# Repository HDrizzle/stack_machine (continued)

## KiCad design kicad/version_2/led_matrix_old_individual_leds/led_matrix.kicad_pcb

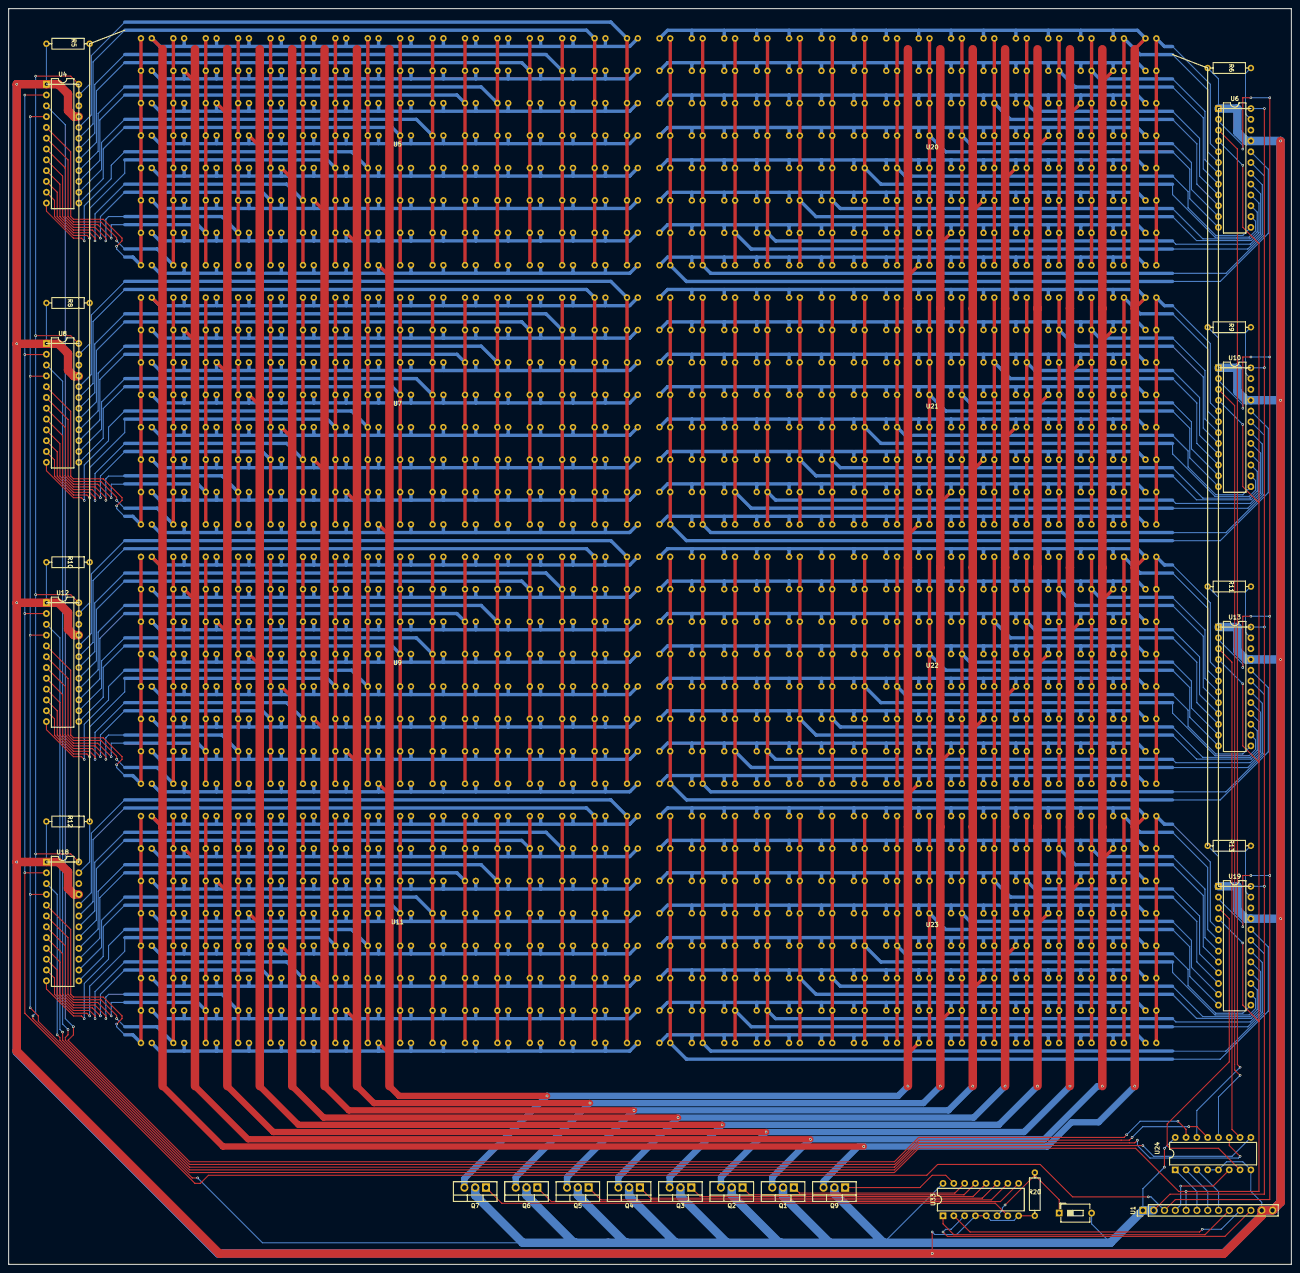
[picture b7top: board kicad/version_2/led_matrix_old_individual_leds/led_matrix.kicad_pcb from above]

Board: 2 copper layers, 301.6 x 295.3 mm, 37 parts (0 on the bottom side), 172 nets.

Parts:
Q1, Q2, Q3, Q4, Q5, Q6, Q7, Q9: IRF540N; TO-220-3_Vertical
R5, R6, R8, R9, R10, R11, R12, R13, R20: R; 0.4_pitch_resistor
SW1: SW_DIP_x01; SW_DIP_SPSTx01_Slide_6.7x4.1mm_W7.62mm_P2.54mm_LowProfile
U1: PinHeader_1x13_P2.54mm_Vertical
U4, U6, U8, U10, U12, U13, U18, U19: DIP-24_W7.62mm
U5, U7, U9, U11: led_block_16_x_8_left
U20, U21, U22, U23: led_block_16_x_8_right
U24, U33: DIP-16_W7.62mm

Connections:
unnamed: Q1.2 (D), Q2.2 (D), Q3.2 (D), Q4.2 (D), Q5.2 (D), Q6.2 (D), Q7.2 (D), Q9.2 (D), SW1.2, U1.1 (V+), U1.2 (V+), U4.24 (V+), U6.24 (V+), U8.24 (V+), U10.24 (V+), U12.24 (V+), U13.24 (V+), U18.24 (V+), U19.24 (V+), U24.16 (V+), U33.16 (V+)
unnamed: Q1.1 (G), U33.14 (Y1)
unnamed: Q1.3 (S), U5.18 (R1), U7.18 (R1), U9.18 (R1), U11.18 (R1), U20.18 (R1), U21.18 (R1), U22.18 (R1), U23.18 (R1)
unnamed: Q2.1 (G), U33.13 (Y2)
unnamed: Q2.3 (S), U5.19 (R2), U7.19 (R2), U9.19 (R2), U11.19 (R2), U20.19 (R2), U21.19 (R2), U22.19 (R2), U23.19 (R2)
unnamed: Q3.1 (G), U33.12 (Y3)
unnamed: Q3.3 (S), U5.20 (R3), U7.20 (R3), U9.20 (R3), U11.20 (R3), U20.20 (R3), U21.20 (R3), U22.20 (R3), U23.20 (R3)
unnamed: Q4.1 (G), U33.11 (Y4)
unnamed: Q4.3 (S), U5.21 (R4), U7.21 (R4), U9.21 (R4), U11.21 (R4), U20.21 (R4), U21.21 (R4), U22.21 (R4), U23.21 (R4)
unnamed: Q5.1 (G), U33.10 (Y5)
unnamed: Q5.3 (S), U5.22 (R5), U7.22 (R5), U9.22 (R5), U11.22 (R5), U20.22 (R5), U21.22 (R5), U22.22 (R5), U23.22 (R5)
unnamed: Q6.1 (G), U33.9 (Y6)
unnamed: Q6.3 (S), U5.23 (R6), U7.23 (R6), U9.23 (R6), U11.23 (R6), U20.23 (R6), U21.23 (R6), U22.23 (R6), U23.23 (R6)
unnamed: Q7.1 (G), U33.7 (Y7)
unnamed: Q7.3 (S), U5.24 (R7), U7.24 (R7), U9.24 (R7), U11.24 (R7), U20.24 (R7), U21.24 (R7), U22.24 (R7), U23.24 (R7)
unnamed: Q9.1 (G), U33.15 (Y0)
unnamed: Q9.3 (S), U5.17 (R0), U7.17 (R0), U9.17 (R0), U11.17 (R0), U20.17 (R0), U21.17 (R0), U22.17 (R0), U23.17 (R0)
unnamed: U1.4 (CLK), U24.6 (E1)
unnamed: U1.3 (Data), U4.2 (D_in), U6.2 (D_in), U8.2 (D_in), U10.2 (D_in), U12.2 (D_in), U13.2 (D_in), U18.2 (D_in), U19.2 (D_in)
unnamed: U1.6 (Driver_A0), U24.1 (A0)
unnamed: U1.7 (Driver_A1), U24.2 (A1)
unnamed: U1.8 (Driver_A2), U24.3 (A2)
unnamed: U1.5 (Driver_LE), U4.4 (LE), U6.4 (LE), U8.4 (LE), U10.4 (LE), U12.4 (LE), U13.4 (LE), U18.4 (LE), U19.4 (LE)
unnamed: U1.9 (Row_A0), U33.1 (A0)
unnamed: U1.10 (Row_A1), U33.2 (A1)
unnamed: U1.11 (Row_A2), U33.3 (A2)
unnamed: U4.5 (O0), U5.1 (C0)
unnamed: U4.6 (O1), U5.2 (C1)
unnamed: U4.7 (O2), U5.3 (C2)
unnamed: U4.8 (O3), U5.4 (C3)
unnamed: U4.9 (O4), U5.5 (C4)
unnamed: U4.10 (O5), U5.6 (C5)
unnamed: U4.11 (O6), U5.7 (C6)
unnamed: U4.12 (O7), U5.8 (C7)
unnamed: U4.13 (O8), U5.9 (C8)
unnamed: U4.14 (O9), U5.10 (C9)
unnamed: U4.15 (O10), U5.11 (C10)
unnamed: U4.16 (O11), U5.12 (C11)
unnamed: U4.17 (O12), U5.13 (C12)
unnamed: U4.18 (O13), U5.14 (C13)
unnamed: U4.19 (O14), U5.15 (C14)
unnamed: U4.20 (O15), U5.16 (C15)
unnamed: R5.1, U4.23 (SET)
unnamed: R6.1, U6.23 (SET)
unnamed: U7.1 (C0), U8.5 (O0)
unnamed: U7.2 (C1), U8.6 (O1)
unnamed: U7.3 (C2), U8.7 (O2)
unnamed: U7.4 (C3), U8.8 (O3)
unnamed: U7.5 (C4), U8.9 (O4)
unnamed: U7.6 (C5), U8.10 (O5)
unnamed: U7.7 (C6), U8.11 (O6)
unnamed: U7.8 (C7), U8.12 (O7)
unnamed: U7.9 (C8), U8.13 (O8)
unnamed: U7.10 (C9), U8.14 (O9)
unnamed: U7.11 (C10), U8.15 (O10)
unnamed: U7.12 (C11), U8.16 (O11)
unnamed: U7.13 (C12), U8.17 (O12)
unnamed: U7.14 (C13), U8.18 (O13)
unnamed: U7.15 (C14), U8.19 (O14)
unnamed: U7.16 (C15), U8.20 (O15)
unnamed: R8.1, U8.23 (SET)
unnamed: U10.3 (CLK), U24.12 (Y3)
unnamed: R5.2, R6.2, R8.2, R9.2, R10.2, R11.2, R12.2, R13.2, R20.2, U1.12 (GND), U1.13 (GND), U4.1 (GND), U4.21 (OE#), U6.1 (GND), U6.21 (OE#), U8.1 (GND), U8.21 (OE#), U10.1 (GND), U10.21 (OE#), U12.1 (GND), U12.21 (OE#), U13.1 (GND), U13.21 (OE#), U18.1 (GND), U18.21 (OE#), U19.1 (GND), U19.21 (OE#), U24.4 (E2#), U24.5 (E3#), U24.8 (GND), U33.4 (E2#), U33.5 (E3#), U33.8 (GND)
unnamed: U10.5 (O0), U21.1 (C0)
unnamed: U10.6 (O1), U21.2 (C1)
unnamed: U10.7 (O2), U21.3 (C2)
unnamed: U10.8 (O3), U21.4 (C3)
unnamed: U10.9 (O4), U21.5 (C4)
unnamed: U10.10 (O5), U21.6 (C5)
unnamed: U10.11 (O6), U21.7 (C6)
unnamed: U10.12 (O7), U21.8 (C7)
unnamed: U10.13 (O8), U21.9 (C8)
unnamed: U10.14 (O9), U21.10 (C9)
unnamed: U10.15 (O10), U21.11 (C10)
unnamed: U10.16 (O11), U21.12 (C11)
unnamed: U10.17 (O12), U21.13 (C12)
unnamed: U10.18 (O13), U21.14 (C13)
unnamed: U10.19 (O14), U21.15 (C14)
unnamed: U10.20 (O15), U21.16 (C15)
unnamed: R9.1, U10.23 (SET)
unnamed: U11.1 (C0), U18.5 (O0)
unnamed: U11.2 (C1), U18.6 (O1)
unnamed: U11.3 (C2), U18.7 (O2)
unnamed: U11.4 (C3), U18.8 (O3)
unnamed: U11.5 (C4), U18.9 (O4)
unnamed: U11.6 (C5), U18.10 (O5)
unnamed: U11.7 (C6), U18.11 (O6)
unnamed: U11.8 (C7), U18.12 (O7)
unnamed: U11.9 (C8), U18.13 (O8)
unnamed: U11.10 (C9), U18.14 (O9)
unnamed: U11.11 (C10), U18.15 (O10)
unnamed: U11.12 (C11), U18.16 (O11)
unnamed: U11.13 (C12), U18.17 (O12)
unnamed: U11.14 (C13), U18.18 (O13)
unnamed: U11.15 (C14), U18.19 (O14)
unnamed: U11.16 (C15), U18.20 (O15)
unnamed: U12.3 (CLK), U24.11 (Y4)
unnamed: U9.1 (C0), U12.5 (O0)
unnamed: U9.2 (C1), U12.6 (O1)
unnamed: U9.3 (C2), U12.7 (O2)
unnamed: U9.4 (C3), U12.8 (O3)
unnamed: U9.5 (C4), U12.9 (O4)
unnamed: U9.6 (C5), U12.10 (O5)
unnamed: U9.7 (C6), U12.11 (O6)
unnamed: U9.8 (C7), U12.12 (O7)
unnamed: U9.9 (C8), U12.13 (O8)
unnamed: U9.10 (C9), U12.14 (O9)
unnamed: U9.11 (C10), U12.15 (O10)
unnamed: U9.12 (C11), U12.16 (O11)
unnamed: U9.13 (C12), U12.17 (O12)
unnamed: U9.14 (C13), U12.18 (O13)
unnamed: U9.15 (C14), U12.19 (O14)
unnamed: U9.16 (C15), U12.20 (O15)
unnamed: R10.1, U12.23 (SET)
unnamed: U13.3 (CLK), U24.10 (Y5)
unnamed: U13.5 (O0), U22.1 (C0)
unnamed: U13.6 (O1), U22.2 (C1)
unnamed: U13.7 (O2), U22.3 (C2)
unnamed: U13.8 (O3), U22.4 (C3)
unnamed: U13.9 (O4), U22.5 (C4)
unnamed: U13.10 (O5), U22.6 (C5)
unnamed: U13.11 (O6), U22.7 (C6)
unnamed: U13.12 (O7), U22.8 (C7)
unnamed: U13.13 (O8), U22.9 (C8)
unnamed: U13.14 (O9), U22.10 (C9)
unnamed: U13.15 (O10), U22.11 (C10)
unnamed: U13.16 (O11), U22.12 (C11)
unnamed: U13.17 (O12), U22.13 (C12)
unnamed: U13.18 (O13), U22.14 (C13)
unnamed: U13.19 (O14), U22.15 (C14)
unnamed: U13.20 (O15), U22.16 (C15)
unnamed: R11.1, U13.23 (SET)
unnamed: U18.3 (CLK), U24.9 (Y6)
unnamed: R12.1, U18.23 (SET)
unnamed: U19.3 (CLK), U24.7 (Y7)
unnamed: U19.5 (O0), U23.1 (C0)
unnamed: U19.6 (O1), U23.2 (C1)
unnamed: U19.7 (O2), U23.3 (C2)
unnamed: U19.8 (O3), U23.4 (C3)
unnamed: U19.9 (O4), U23.5 (C4)
unnamed: U19.10 (O5), U23.6 (C5)
unnamed: U19.11 (O6), U23.7 (C6)
unnamed: U19.12 (O7), U23.8 (C7)
unnamed: U19.13 (O8), U23.9 (C8)
unnamed: U19.14 (O9), U23.10 (C9)
unnamed: U19.15 (O10), U23.11 (C10)
unnamed: U19.16 (O11), U23.12 (C11)
unnamed: U19.17 (O12), U23.13 (C12)
unnamed: U19.18 (O13), U23.14 (C13)
unnamed: U19.19 (O14), U23.15 (C14)
unnamed: U19.20 (O15), U23.16 (C15)
unnamed: R13.1, U19.23 (SET)
unnamed: U6.5 (O0), U20.1 (C0)
unnamed: U6.6 (O1), U20.2 (C1)
unnamed: U6.7 (O2), U20.3 (C2)
unnamed: U6.8 (O3), U20.4 (C3)
unnamed: U6.9 (O4), U20.5 (C4)
unnamed: U6.10 (O5), U20.6 (C5)
unnamed: U6.11 (O6), U20.7 (C6)
unnamed: U6.12 (O7), U20.8 (C7)
unnamed: U6.13 (O8), U20.9 (C8)
unnamed: U6.14 (O9), U20.10 (C9)
unnamed: U6.15 (O10), U20.11 (C10)
unnamed: U6.16 (O11), U20.12 (C11)
unnamed: U6.17 (O12), U20.13 (C12)
unnamed: U6.18 (O13), U20.14 (C13)
unnamed: U6.19 (O14), U20.15 (C14)
unnamed: U6.20 (O15), U20.16 (C15)
unnamed: U4.3 (CLK), U24.15 (Y0)
unnamed: U6.3 (CLK), U24.14 (Y1)
unnamed: U8.3 (CLK), U24.13 (Y2)
unnamed: R20.1, SW1.1, U33.6 (E1)

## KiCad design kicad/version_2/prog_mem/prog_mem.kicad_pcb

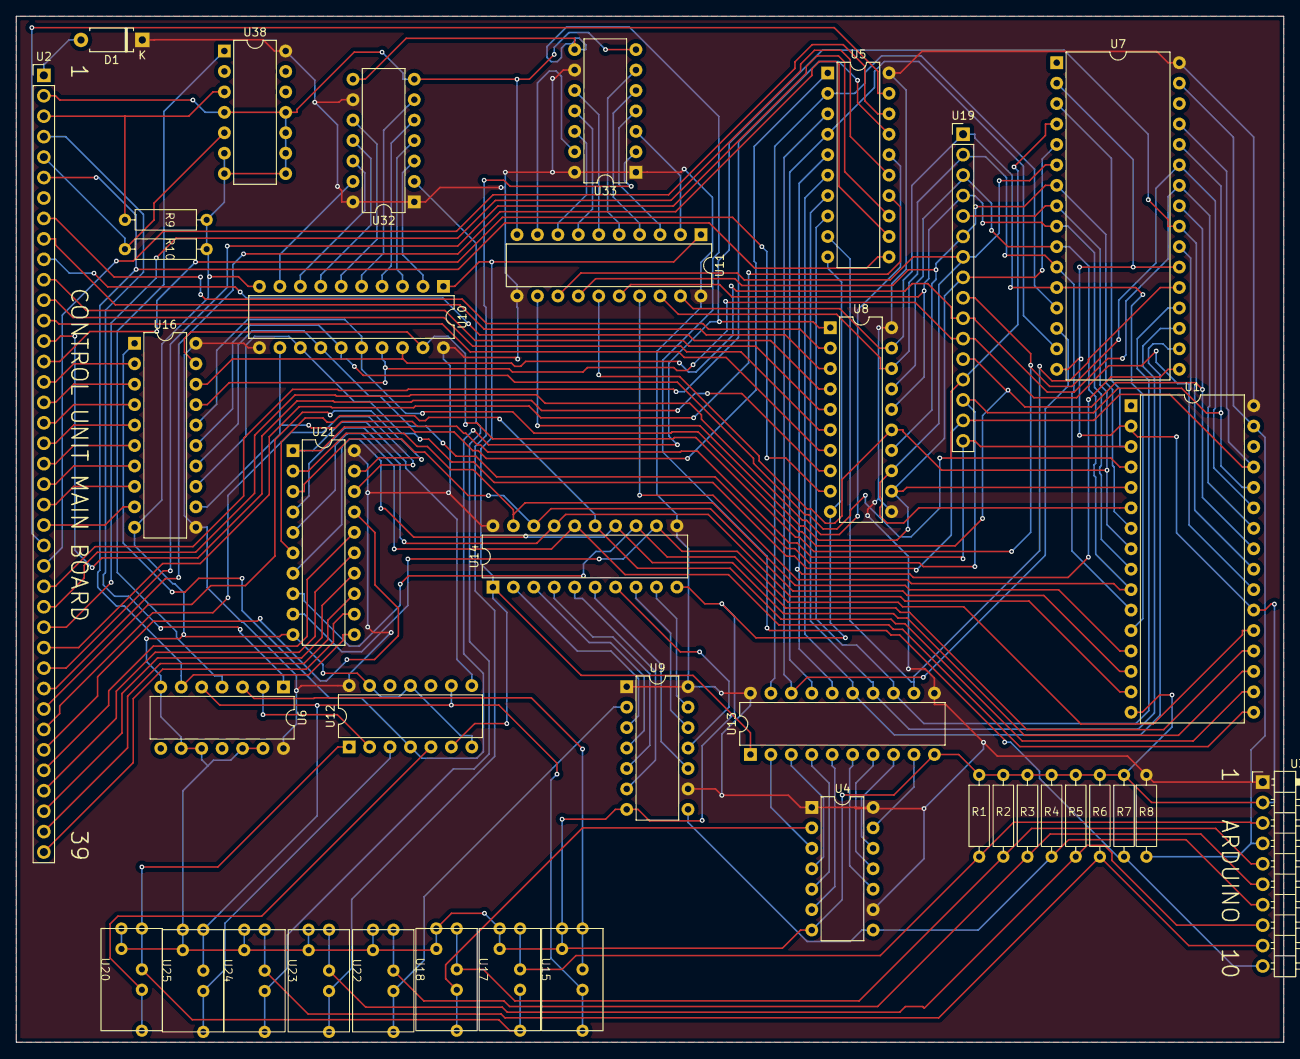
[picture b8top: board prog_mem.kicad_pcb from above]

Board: 2 copper layers, 157.5 x 127.5 mm, 39 parts (0 on the bottom side), 125 nets.

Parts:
D1: D; D_A-405_P7.62mm_Horizontal
R1, R2, R3, R4, R5, R6, R7, R8, R9, R10: 10k; 0.4_pitch_resistor
U1, U7: DIP-32_W15.24mm
U2: PinHeader_1x39_P2.54mm_Vertical
U3: PinHeader_1x10_P2.54mm_Horizontal
U4, U6, U9, U12, U32, U33, U38: DIP-14_W7.62mm
U5, U8, U10, U11, U13, U14, U16, U21: DIP-20_W7.62mm
U15, U17, U18, U20, U22, U23, U24, U25: jumper
U19: PinHeader_1x16_P2.54mm_Vertical

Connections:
unnamed: D1.2 (A), U2.1 (V+)
unnamed: D1.1 (K), R8.1, U1.32 (V+), U3.1 (V+), U4.1 (A), U4.9 (CLR#), U4.14 (V+), U5.20 (V+), U6.14 (V+), U7.32 (V+), U8.11 (CLK), U8.20 (V+), U9.1 (A), U9.9 (CLR#), U9.14 (V+), U10.11 (CLK), U10.20 (V+), U11.11 (CLK), U11.20 (V+), U12.14 (V+), U13.11 (CLK), U13.20 (V+), U14.11 (CLK), U14.20 (V+), U16.11 (CLK), U16.20 (V+), U21.20 (V+), U32.1 (A), U32.9 (CLR#), U32.14 (V+), U33.1 (A), U33.9 (CLR#), U33.14 (V+), U38.14 (V+)
unnamed: U1.12 (A0), U7.12 (A0), U8.19 (Q0), U11.19 (Q0), U19.1 (0)
unnamed: U1.11 (A1), U7.11 (A1), U8.18 (Q1), U11.18 (Q1), U19.2 (1)
unnamed: U1.10 (A2), U7.10 (A2), U8.17 (Q2), U11.17 (Q2), U19.3 (2)
unnamed: U1.9 (A3), U7.9 (A3), U8.16 (Q3), U11.16 (Q3), U19.4 (3)
unnamed: U1.8 (A4), U7.8 (A4), U8.15 (Q4), U11.15 (Q4), U19.5 (4)
unnamed: U1.7 (A5), U7.7 (A5), U8.14 (Q5), U11.14 (Q5), U19.6 (5)
unnamed: U1.6 (A6), U7.6 (A6), U8.13 (Q6), U11.13 (Q6), U19.7 (6)
unnamed: U1.5 (A7), U7.5 (A7), U8.12 (Q7), U11.12 (Q7), U19.8 (7)
unnamed: U1.27 (A8), U7.27 (A8), U10.19 (Q0), U16.19 (Q0), U19.9 (8)
unnamed: U1.26 (A9), U7.26 (A9), U10.18 (Q1), U16.18 (Q1), U19.10 (9)
unnamed: U1.23 (A10), U7.23 (A10), U10.17 (Q2), U16.17 (Q2), U19.11 (10)
unnamed: U1.25 (A11), U7.25 (A11), U10.16 (Q3), U16.16 (Q3), U19.12 (11)
unnamed: U1.4 (A12), U7.4 (A12), U10.15 (Q4), U16.15 (Q4), U19.13 (12)
unnamed: U1.28 (A13), U7.28 (A13), U10.14 (Q5), U16.14 (Q5), U19.14 (13)
unnamed: U1.29 (A14), U7.29 (A14), U10.13 (Q6), U16.13 (Q6), U19.15 (14)
unnamed: U1.3 (A15), U7.3 (A15), U10.12 (Q7), U16.12 (Q7), U19.16 (15)
unnamed: R1.1, R2.1, R3.1, R4.1, R5.1, R6.1, R7.1, R9.1, R10.1, U1.2 (A16), U1.16 (GND), U1.22 (CE#), U2.2 (GND), U3.2 (GND), U4.7 (GND), U5.10 (GND), U6.7 (GND), U6.9 (4B), U6.10 (4A), U6.12 (3B), U6.13 (3A), U7.2 (A16), U7.16 (GND), U7.22 (CE#), U8.10 (GND), U9.7 (GND), U10.10 (GND), U11.10 (GND), U12.7 (GND), U12.11 (I4), U12.13 (I5), U13.10 (GND), U14.10 (GND), U15.2 (GND), U16.10 (GND), U17.2 (GND), U18.2 (GND), U20.2 (GND), U21.10 (GND), U22.2 (GND), U23.2 (GND), U24.2 (GND), U25.2 (GND), U32.7 (GND), U33.7 (GND), U38.4 (0RESET), U38.6 (0SET), U38.7 (GND), U38.8 (1SET), U38.9 (1D), U38.10 (1RESET), U38.11 (1CLK)
unnamed: U1.13 (DQ0), U14.19 (Q0), U21.2 (D0)
unnamed: U1.14 (DQ1), U14.18 (Q1), U21.3 (D1)
unnamed: U1.15 (DQ2), U14.17 (Q2), U21.4 (D2)
unnamed: U1.17 (DQ3), U14.16 (Q3), U21.5 (D3)
unnamed: U1.18 (DQ4), U14.15 (Q4), U21.6 (D4)
unnamed: U1.19 (DQ5), U14.14 (Q5), U21.7 (D5)
unnamed: U1.20 (DQ6), U14.13 (Q6), U21.8 (D6)
unnamed: U1.21 (DQ7), U14.12 (Q7), U21.9 (D7)
unnamed: U1.24 (OE#), U7.24 (OE#), U8.1 (OE#), U12.4 (O1), U16.1 (OE#)
unnamed: R8.2, U1.31 (WE#), U3.4 (WE#), U7.31 (WE#)
unnamed: U2.8 (A0), U8.2 (D0)
unnamed: U2.9 (A1), U8.3 (D1)
unnamed: U2.10 (A2), U8.4 (D2)
unnamed: U2.11 (A3), U8.5 (D3)
unnamed: U2.12 (A4), U8.6 (D4)
unnamed: U2.13 (A5), U8.7 (D5)
unnamed: U2.14 (A6), U8.8 (D6)
unnamed: U2.15 (A7), U8.9 (D7)
unnamed: R9.2, U2.3 (CLK), U38.3 (0CLK)
unnamed: U2.24 (D0), U5.19 (Q0)
unnamed: U2.25 (D1), U5.18 (Q1)
unnamed: U2.26 (D2), U5.17 (Q2)
unnamed: U2.27 (D3), U5.16 (Q3)
unnamed: U2.28 (D4), U5.15 (Q4)
unnamed: U2.29 (D5), U5.14 (Q5)
unnamed: U2.30 (D6), U5.13 (Q6)
unnamed: U2.31 (D7), U5.12 (Q7)
unnamed: U2.32 (D8), U21.19 (Q0)
unnamed: U2.33 (D9), U21.18 (Q1)
unnamed: U2.34 (D10), U21.17 (Q2)
unnamed: U2.35 (D11), U21.16 (Q3)
unnamed: U2.36 (D12), U21.15 (Q4)
unnamed: U2.37 (D13), U21.14 (Q5)
unnamed: U2.38 (D14), U21.13 (Q6)
unnamed: U2.39 (D15), U21.12 (Q7)
unnamed: U2.6 (Done), U5.11 (CLK), U6.6 (2Q), U21.11 (CLK)
unnamed: R10.2, U2.5 (Read), U38.5 (0D)
unnamed: U2.4 (Read_enable), U6.1 (1A)
unnamed: R7.2, U3.10 (A_CLK), U32.8 (CLK), U33.8 (CLK)
unnamed: R4.2, U3.7 (D_CLK), U4.8 (CLK), U9.8 (CLK)
unnamed: U10.2 (D0), U32.3 (Q0)
unnamed: U10.3 (D1), U32.4 (Q1)
unnamed: U10.4 (D2), U32.5 (Q2)
unnamed: U10.5 (D3), U32.6 (Q3)
unnamed: U10.6 (D4), U32.10 (Q4)
unnamed: U10.7 (D5), U32.11 (Q5)
unnamed: U10.8 (D6), U32.12 (Q6)
unnamed: U10.9 (D7), U32.13 (Q7)
unnamed: U10.1 (OE#), U11.1 (OE#), U12.6 (O2), U13.1 (OE#), U14.1 (OE#)
unnamed: U11.2 (D0), U33.3 (Q0)
unnamed: U11.3 (D1), U33.4 (Q1)
unnamed: U11.4 (D2), U33.5 (Q2)
unnamed: U11.5 (D3), U33.6 (Q3)
unnamed: U11.6 (D4), U33.10 (Q4)
unnamed: U11.7 (D5), U33.11 (Q5)
unnamed: U11.8 (D6), U33.12 (Q6)
unnamed: U11.9 (D7), U33.13 (Q7)
unnamed: U5.1 (OE#), U12.8 (03), U21.1 (OE#)
unnamed: U12.1 (I0), U17.3 (OUT), U20.1 (IN)
unnamed: U12.3 (I1), U25.3 (OUT)
unnamed: U12.5 (I2), U20.3 (OUT)
unnamed: U6.5 (2B), U12.9 (I3), U15.3 (OUT), U25.1 (IN)
unnamed: U6.2 (1B), U12.2 (O0)
unnamed: U4.3 (Q0), U13.2 (D0)
unnamed: U4.4 (Q1), U13.3 (D1)
unnamed: U4.5 (Q2), U13.4 (D2)
unnamed: U4.6 (Q3), U13.5 (D3)
unnamed: U4.10 (Q4), U13.6 (D4)
unnamed: U4.11 (Q5), U13.7 (D5)
unnamed: U4.12 (Q6), U13.8 (D6)
unnamed: U4.13 (Q7), U13.9 (D7)
unnamed: U5.2 (D0), U7.13 (DQ0), U13.19 (Q0)
unnamed: U5.3 (D1), U7.14 (DQ1), U13.18 (Q1)
unnamed: U5.4 (D2), U7.15 (DQ2), U13.17 (Q2)
unnamed: U5.5 (D3), U7.17 (DQ3), U13.16 (Q3)
unnamed: U5.6 (D4), U7.18 (DQ4), U13.15 (Q4)
unnamed: U5.7 (D5), U7.19 (DQ5), U13.14 (Q5)
unnamed: U5.8 (D6), U7.20 (DQ6), U13.13 (Q6)
unnamed: U5.9 (D7), U7.21 (DQ7), U13.12 (Q7)
unnamed: U9.3 (Q0), U14.2 (D0)
unnamed: U9.4 (Q1), U14.3 (D1)
unnamed: U9.5 (Q2), U14.4 (D2)
unnamed: U9.6 (Q3), U14.5 (D3)
unnamed: U9.10 (Q4), U14.6 (D4)
unnamed: U9.11 (Q5), U14.7 (D5)
unnamed: U9.12 (Q6), U14.8 (D6)
unnamed: U9.13 (Q7), U14.9 (D7)
unnamed: U6.3 (1Q), U15.1 (IN)
unnamed: U2.16 (A8), U16.2 (D0)
unnamed: U2.17 (A9), U16.3 (D1)
unnamed: U2.18 (A10), U16.4 (D2)
unnamed: U2.19 (A11), U16.5 (D3)
unnamed: U2.20 (A12), U16.6 (D4)
unnamed: U2.21 (A13), U16.7 (D5)
unnamed: U2.22 (A14), U16.8 (D6)
unnamed: U2.23 (A15), U16.9 (D7)
unnamed: R1.2, U3.3 (Write_mode_enable), U17.1 (IN)
unnamed: R2.2, U3.5 (D_0-7), U18.1 (IN)
unnamed: U4.2 (B), U18.3 (OUT)
unnamed: R3.2, U3.6 (D_8-15), U22.1 (IN)
unnamed: U9.2 (B), U22.3 (OUT)
unnamed: R5.2, U3.8 (A_0-7), U23.1 (IN)
unnamed: U23.3 (OUT), U33.2 (B)
unnamed: R6.2, U3.9 (A_8-15), U24.1 (IN)
unnamed: U24.3 (OUT), U32.2 (B)
unnamed: U6.4 (2A), U38.1 (0Q)
